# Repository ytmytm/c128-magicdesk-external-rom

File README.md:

# MagicDesk-like External ROM cartridge for C128

This is a clone of [Magic Desk 512k](https://github.com/msolajic/c64-magic-desk-512k) by Marko Šolajić
converted to KiCad 6 format and modified to work as an External ROM cartridge for C128 and map 32K of ROM at a time.

It is supported by [Magic cartridge generator](https://bitbucket.org/zzarko/magic-cartridge-generator/src/main/).

## Other options

There are two other projects [Magic Desk 128](https://github.com/RetroNynjah/Magic-Desk-128) and [Gmod2 (128)](https://www.freepascal.org/~daniel/gmod2/)
with a similar goal, but both map only 16K at a time. This makes it impossible e.g. to put The Servant on such cartridge.

## Why

It just seems much more useful in C128 mode to have whole 32K available - just like Internal Function ROM, but easily switched.
Since MMU can bank in/out both 16K halves ($8000-$BFFF) and ($C000-$FFFF) separately it seems that e.g. GEOS 128 could run directly from ROM bypassing any boot or loading parts.

## Hardware

The [schematic is here](kicad/plots/c128-magicdesk.pdf).

The main difference to C64 version is that this cartridge is meant for C128, so `/EXROM` signal is no longer connected to prevent from entering C64 mode automatically.

Two diodes and a pullup resistor perform AND function on `/ROML` and `/ROMH` to map 32K at a time ($8000-$FFFF).

Because the bank size is now 32K instead of 8K the lowest two bits of control register are not connected.

[kicad](kicad/) folder contains all the KiCad 6.0 project files and [kicad/plots](kicad/plots) all the Gerber files needed to produce PCB.

Please read the notes from the [original project](https://github.com/msolajic/c64-magic-desk-512k). The jumper configuration for various EPROMS/EEPROMS/FLASH chips is exactly the same, as well as possible expansion to 1MB.

## Programming

Data from ROM will appear as External Function ROM mapped in $8000-$FFFF area (32K).

ROM banks can be changed from BASIC.

```
BANK15:POKEDEC("DE00"),4*<rom bank>
```

There are 16 banks in a 512K EEPROM and 32 banks if you piggy-back two of them and connect `/CE2` signal as described for C64 Magic Desk 512K.

RESET will always enable bank 0.

It's easy to check the ROM data from C128 monitor, just use `8` as the bank number:

```
M 88000 880FF
```

Reading from $DE00 register will switch bank to a random value (what happened to be on the data bus), don't do that.

## Cartrige ROM generator

[Magic cartridge generator](https://bitbucket.org/zzarko/magic-cartridge-generator/src/main/) supports 32K banks, use `-832` option instead of `-8` when building ROM image.

A simple code snippet for a true C128 cartridge (internal/external function ROM) code to load and start BASIC program can be found on [World of Jani page](http://blog.worldofjani.com/?p=1600).

[Gmod2 Commodore 128 technical manual](https://www.freepascal.org/~daniel/gmod2/gmod2-c128.pdf) is also a useful resource.

You can also put The Servant on it. Preferably [the updated one that supports SD2IEC subdirectories and disk images](https://github.com/ytmytm/c128-theservant-sd2iec).

## Emulator Support

None yet :)

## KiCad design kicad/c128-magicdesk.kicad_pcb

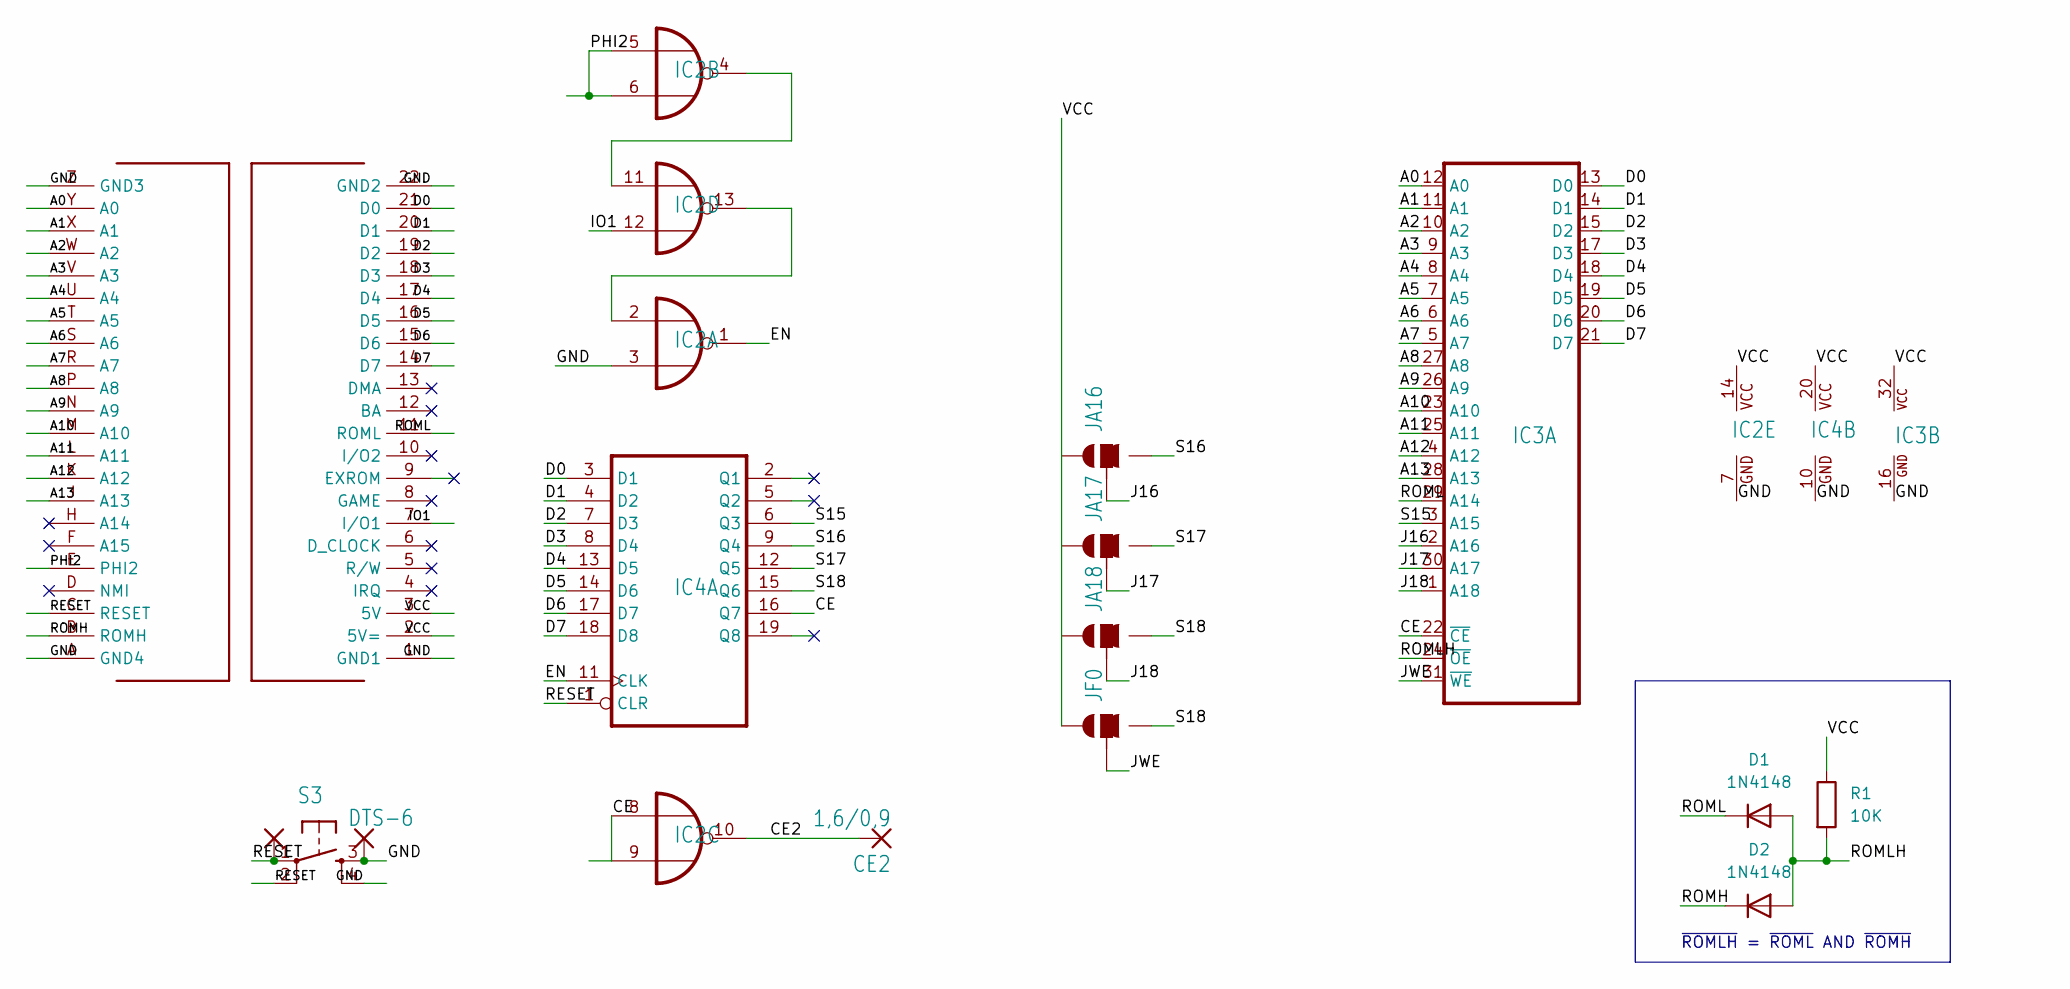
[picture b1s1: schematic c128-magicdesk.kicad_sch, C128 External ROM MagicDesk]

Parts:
CE2: 1,6/0,9; 1,6_0,9
D1, D2: 1N4148; D_DO-35_SOD27_P7.62mm_Horizontal
IC2: 74LS02; DIL14
IC3: 29F040; DIL32-6
IC4: 74LS273; DIL20
JA16, JA17, JA18: SOLDERJUMPER_2WAYS; SJ_3
JF0: SOLDERJUMPER_2WAYS; SJ_3
PAD1, PAD2: SMD5; SMD2,54-5,08
R1: 10K; R_Axial_DIN0207_L6.3mm_D2.5mm_P10.16mm_Horizontal
S3: DTS-6
U$1: C64_EXPANSION__CARTRIDGE

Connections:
/A0: IC3.12 (A0), U$1.Y (A0)
/A1: IC3.11 (A1), U$1.X (A1)
/A2: IC3.10 (A2), U$1.W (A2)
/A3: IC3.9 (A3), U$1.V (A3)
/A4: IC3.8 (A4), U$1.U (A4)
/A5: IC3.7 (A5), U$1.T (A5)
/A6: IC3.6 (A6), U$1.S (A6)
/A7: IC3.5 (A7), U$1.R (A7)
/A8: IC3.27 (A8), U$1.P (A8)
/A9: IC3.26 (A9), U$1.N (A9)
/A10: IC3.23 (A10), U$1.M (A10)
/A11: IC3.25 (A11), U$1.L (A11)
/A12: IC3.4 (A12), U$1.K (A12)
/A13: IC3.28 (A13), U$1.J (A13)
/CE: IC2.8 (I0), IC2.9 (I1), IC3.22 (~CE), IC4.16 (Q7)
/CE2: CE2.1, IC2.10 (O)
/D0: IC3.13 (D0), IC4.3 (D1), U$1.21 (D0)
/D1: IC3.14 (D1), IC4.4 (D2), U$1.20 (D1)
/D2: IC3.15 (D2), IC4.7 (D3), U$1.19 (D2)
/D3: IC3.17 (D3), IC4.8 (D4), U$1.18 (D3)
/D4: IC3.18 (D4), IC4.13 (D5), U$1.17 (D4)
/D5: IC3.19 (D5), IC4.14 (D6), U$1.16 (D5)
/D6: IC3.20 (D6), IC4.17 (D7), U$1.15 (D6)
/D7: IC3.21 (D7), IC4.18 (D8), U$1.14 (D7)
/EN: IC2.1 (O), IC4.11 (CLK)
/GND: IC2.3 (I1), IC2.7 (GND), IC3.16 (GND), IC4.10 (GND), PAD2.1, S3.3, S3.4, U$1.1 (GND1), U$1.22 (GND2), U$1.A (GND4), U$1.Z (GND3)
/IO1: IC2.12 (I1), U$1.7 (I/O1)
/J16: IC3.2 (A16), JA16.2
/J17: IC3.30 (A17), JA17.2
/J18: IC3.1 (A18), JA18.2
/JWE: IC3.31 (~WE), JF0.2
/PHI2: IC2.5 (I0), IC2.6 (I1), U$1.E (PHI2)
/RESET: IC4.1 (CLR), PAD1.1, S3.1, S3.2, U$1.C (RESET)
/ROMH: D2.1 (K), U$1.B (ROMH)
/ROML: D1.1 (K), IC3.29 (A14), U$1.11 (ROML)
/ROMLH: D1.2 (A), D2.2 (A), IC3.24 (~OE), R1.2
/S15: IC3.3 (A15), IC4.6 (Q3)
/S16: IC4.9 (Q4), JA16.3
/S17: IC4.12 (Q5), JA17.3
/S18: IC4.15 (Q6), JA18.3, JF0.3
/VCC: IC2.14 (VCC), IC3.32 (VCC), IC4.20 (VCC), JA16.1, JA17.1, JA18.1, JF0.1, R1.1, U$1.2 (5V=), U$1.3 (5V)
unnamed: IC2.4 (O), IC2.11 (I0)
unnamed: IC2.2 (I0), IC2.13 (O)

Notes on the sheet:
~{ROMLH} = ~{ROML} AND ~{ROMH}

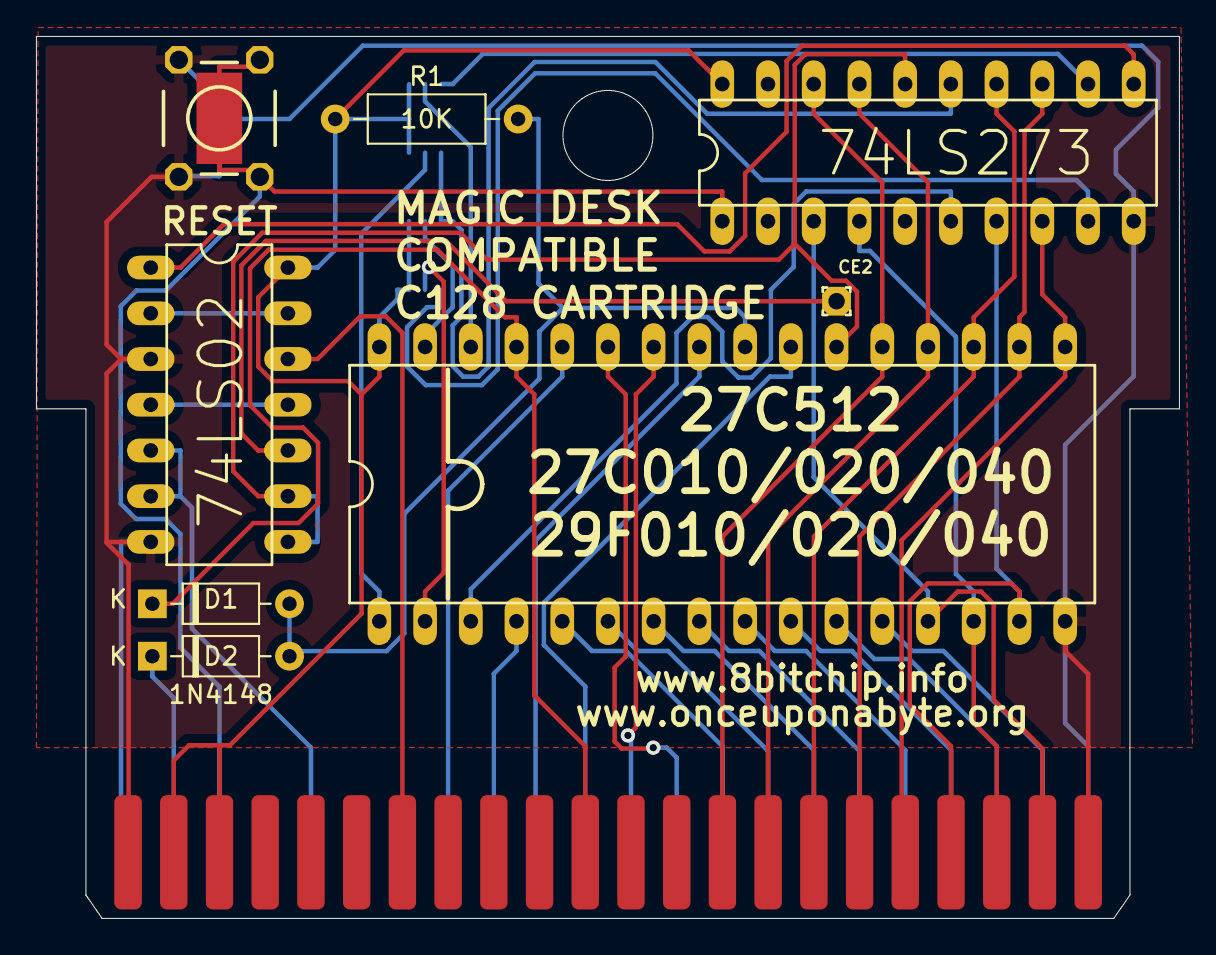
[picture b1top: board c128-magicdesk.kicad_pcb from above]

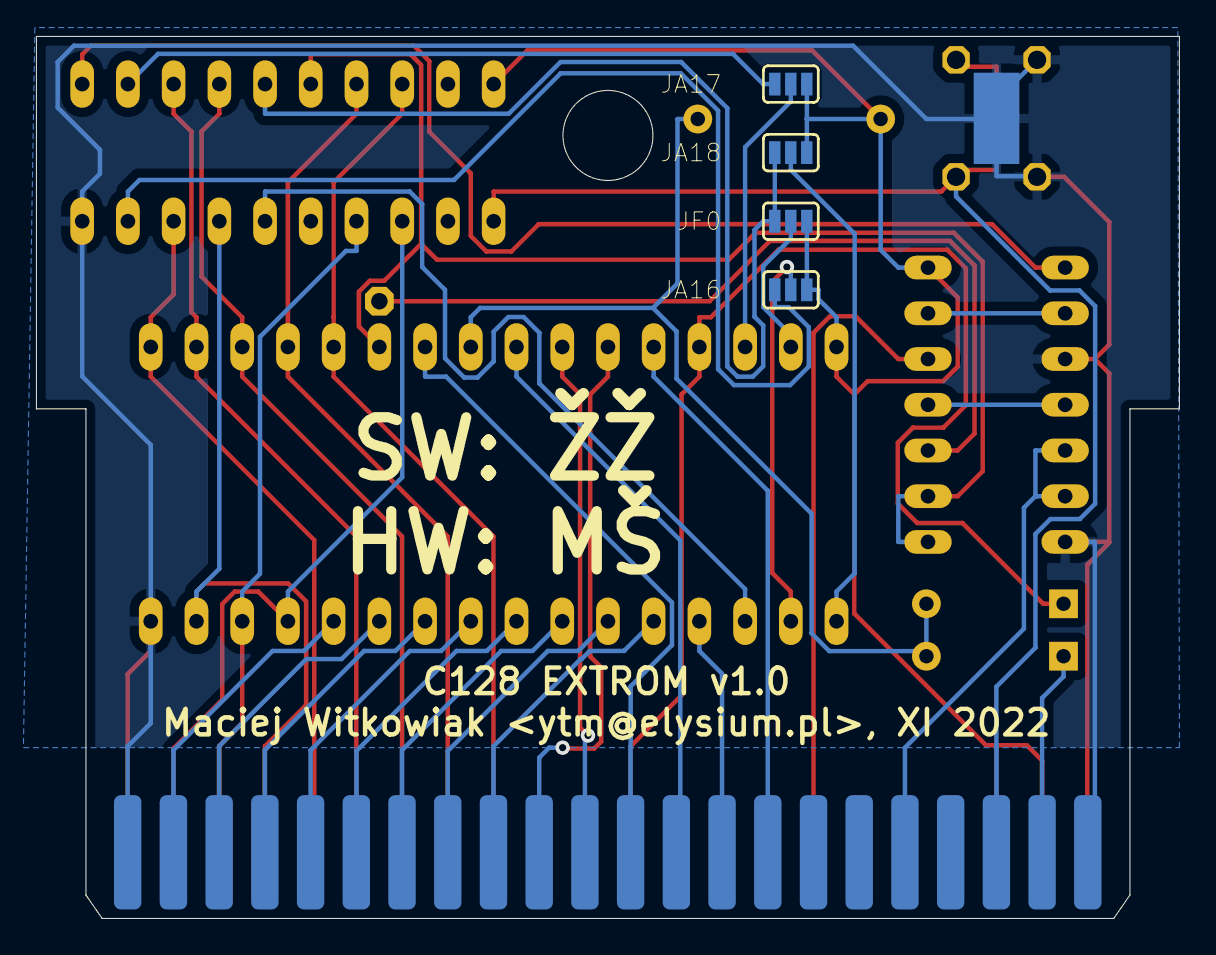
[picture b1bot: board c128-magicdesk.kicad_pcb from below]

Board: 2 copper layers, 63.5 x 49.0 mm, 15 parts (5 on the bottom side), 43 nets.

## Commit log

2023-01-03 typo
2023-01-03 more info
2023-01-03 more links
2023-01-03 work derived from GNU GPL-3.0 licensed project
2023-01-14 info about magic cartridge generator fork
2024-04-13 docs update, cartridge supported in the upstream software
